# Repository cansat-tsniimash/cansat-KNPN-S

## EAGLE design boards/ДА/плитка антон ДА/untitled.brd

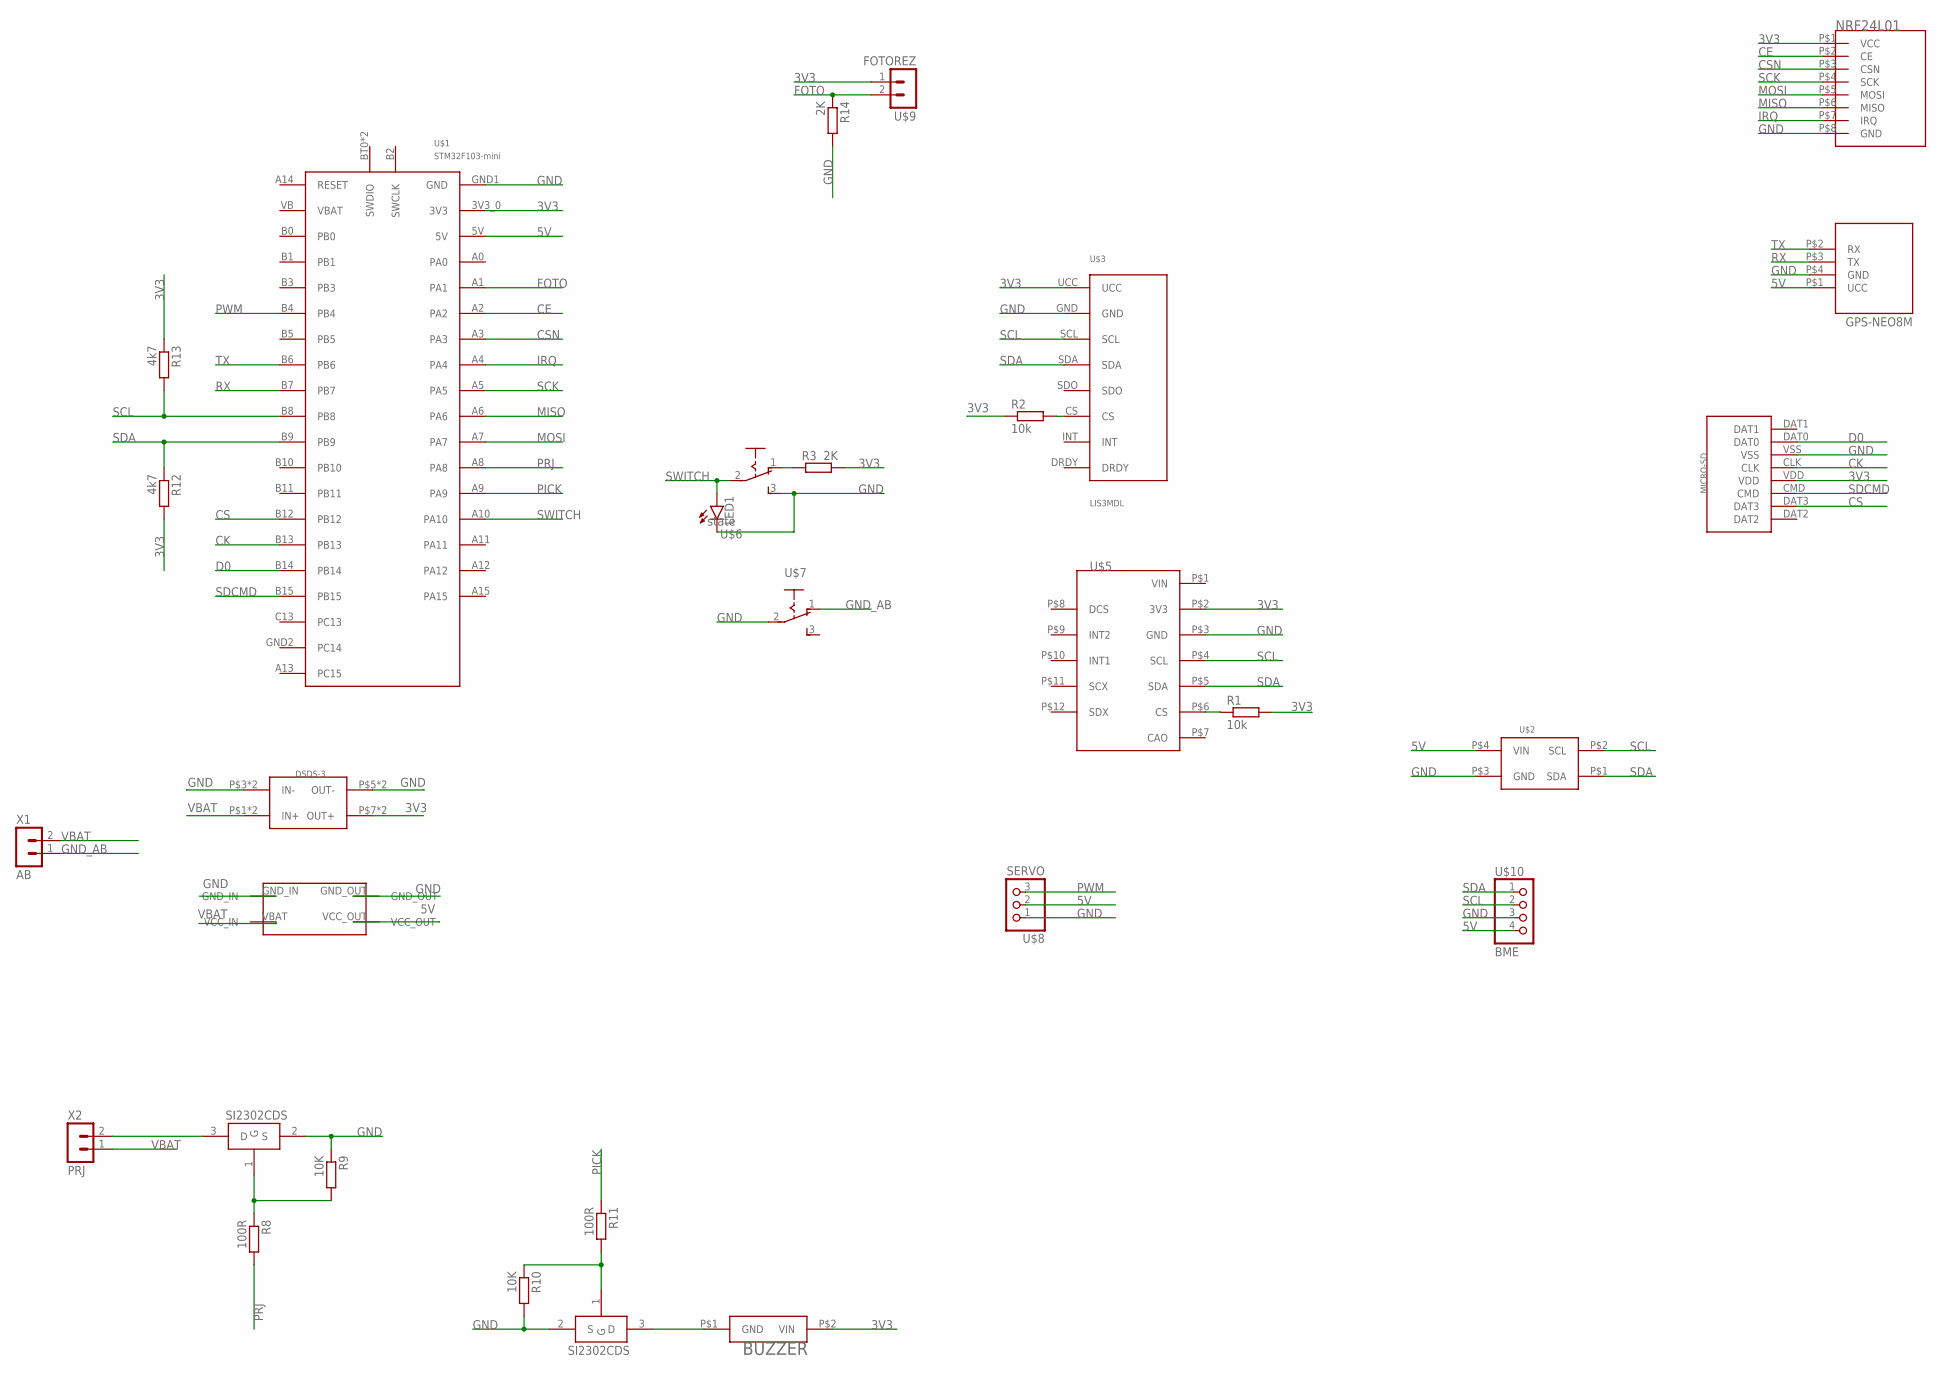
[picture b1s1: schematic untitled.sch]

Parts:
BUZZER: BUZZERS8R6; BUZZER-S8R12
DSDS-3: MP1584-B
DSDS-5: DS-DS_5V
GPS-NEO8M: GPS-NEO8M; GPS-NEO7M
LED1: LEDCHIP-LED0603; CHIP-LED0603
MICRO-SD: SD
NRF24L01: NRF24L01_ML01SP4
R1, R2: 10k; R0603
R3, R14: 2K; R0603
R8, R11: 100R; R0603
R9, R10: 10K; R0603
R12, R13: 4k7; R0603
U$1: STM32F103-mini; BLUEPILL2
U$2: BME280BME280-PINS-ONLY; BME280-PINS-ONLY
U$3: LIS3MDL
U$4, U$12: SI2302CDS; SOT23-3
U$5: LSM6DS3-GY
U$6: state; SWITCH_MSS
U$7: UNICS-SWITCHSS_12D11; SS_12D11
U$8: SERVO; 53047-03
U$9: FOTOREZ; 53047-02
U$10: BME; 53047-04
X1: AB; JST-2-2.5
X2: PRJ; JST-2-2.5

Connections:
3V3: BUZZER.P$2 (VIN), DSDS-3.P$7 (OUT+), DSDS-3.P$8 (OUT+), MICRO-SD.VDD, NRF24L01.P$1 (VCC), R1.2, R2.1, R3.1, R12.2, R13.1, U$1.3V3_0 (3V3), U$3.UCC, U$5.P$2 (3V3), U$9.1
5V: DSDS-5.VCC_OUT, GPS-NEO8M.P$1 (UCC), U$1.5V, U$2.P$4 (VIN), U$8.2, U$10.4
CE: NRF24L01.P$2 (CE), U$1.A2
CK: MICRO-SD.CLK, U$1.B13
CS: MICRO-SD.DAT3, U$1.B12
CSN: NRF24L01.P$3 (CSN), U$1.A3
D0: MICRO-SD.DAT0, U$1.B14
FOTO: R14.1, U$1.A1, U$9.2
GND: DSDS-3.P$3 (IN-), DSDS-3.P$4 (IN-), DSDS-3.P$5 (OUT-), DSDS-3.P$6 (OUT-), DSDS-5.GND_IN, DSDS-5.GND_OUT, GPS-NEO8M.P$4 (GND), LED1.C, MICRO-SD.VSS, NRF24L01.P$8 (GND), R9.1, R10.2, R14.2, U$1.GND1 (GND), U$2.P$3 (GND), U$3.GND, U$4.2 (S), U$5.P$3 (GND), U$6.3 (S), U$7.2, U$8.1, U$10.3, U$12.2 (S)
GND_AB: U$7.1 (O), X1.1
IRQ: NRF24L01.P$7 (IRQ), U$1.A4
MISO: NRF24L01.P$6 (MISO), U$1.A6
MOSI: NRF24L01.P$5 (MOSI), U$1.A7
unnamed: R3.2, U$6.1 (O)
unnamed: R1.1, U$5.P$6 (CS)
unnamed: BUZZER.P$1 (GND), U$4.3 (D)
unnamed: R8.1, R9.2, U$12.1 (G)
unnamed: U$12.3 (D), X2.2
unnamed: R10.1, R11.2, U$4.1 (G)
unnamed: R2.2, U$3.CS
PICK: R11.1, U$1.A9
PRJ: R8.2, U$1.A8
PWM: U$1.B4, U$8.3
RX: GPS-NEO8M.P$3 (TX), U$1.B7
SCK: NRF24L01.P$4 (SCK), U$1.A5
SCL: R13.2, U$1.B8, U$2.P$2 (SCL), U$3.SCL, U$5.P$4 (SCL), U$10.2
SDA: R12.1, U$1.B9, U$2.P$1 (SDA), U$3.SDA, U$5.P$5 (SDA), U$10.1
SDCMD: MICRO-SD.CMD, U$1.B15
SWITCH: LED1.A, U$1.A10, U$6.2
TX: GPS-NEO8M.P$2 (RX), U$1.B6
VBAT: DSDS-3.P$1 (IN+), DSDS-3.P$2 (IN+), DSDS-5.VBAT (VCC_IN), X1.2, X2.1

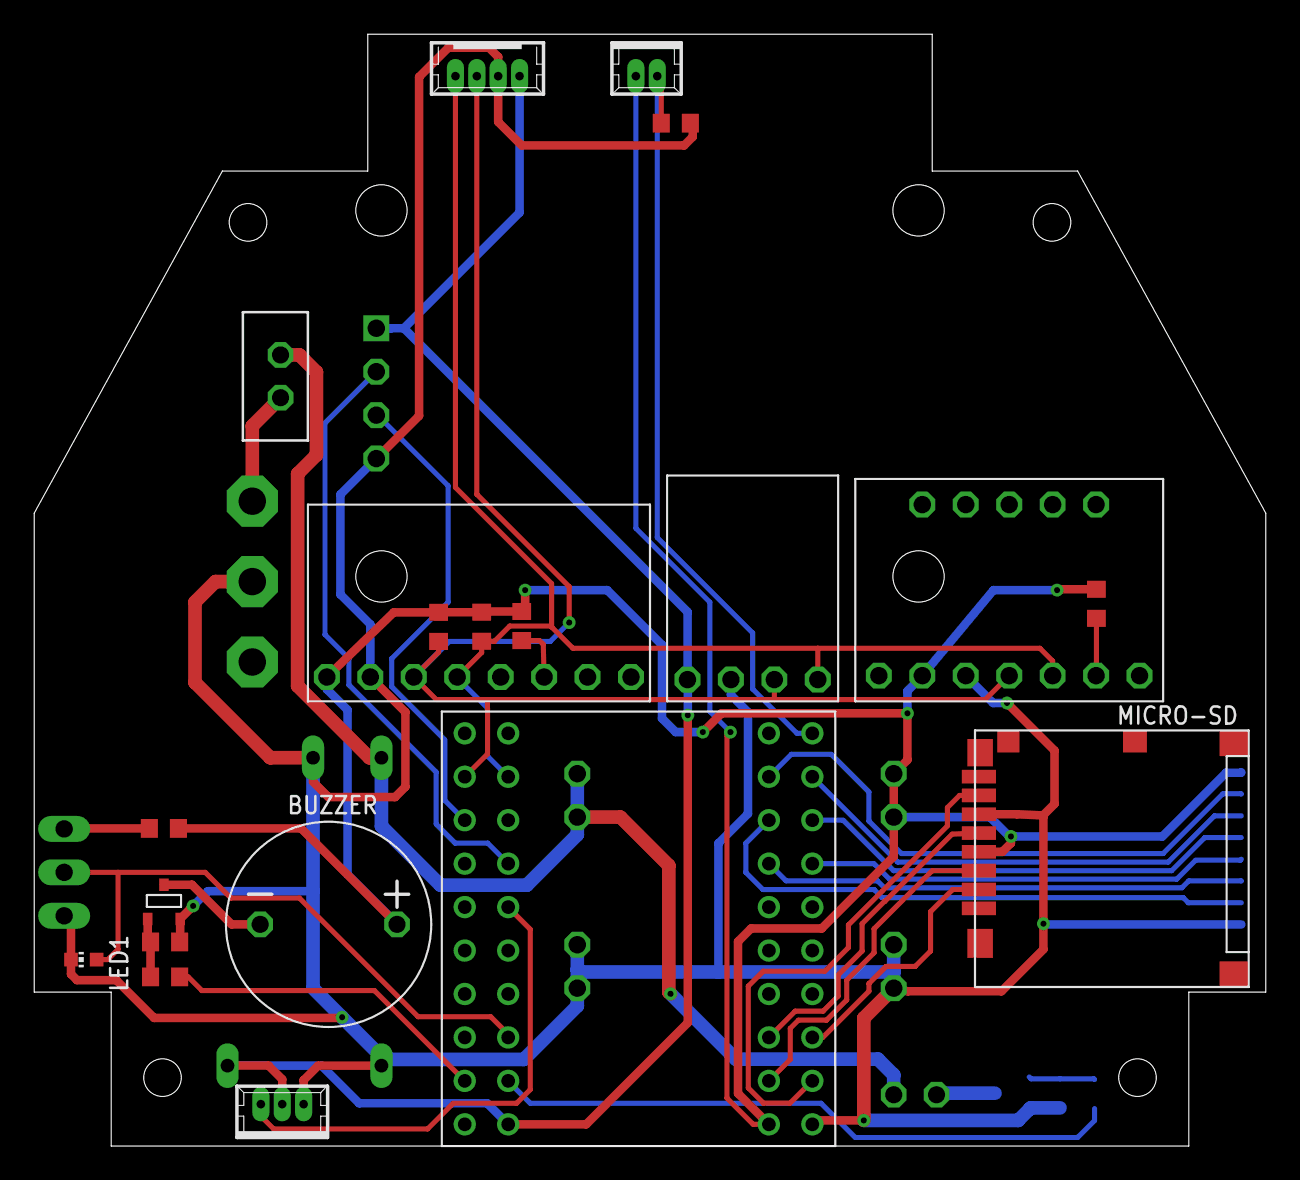
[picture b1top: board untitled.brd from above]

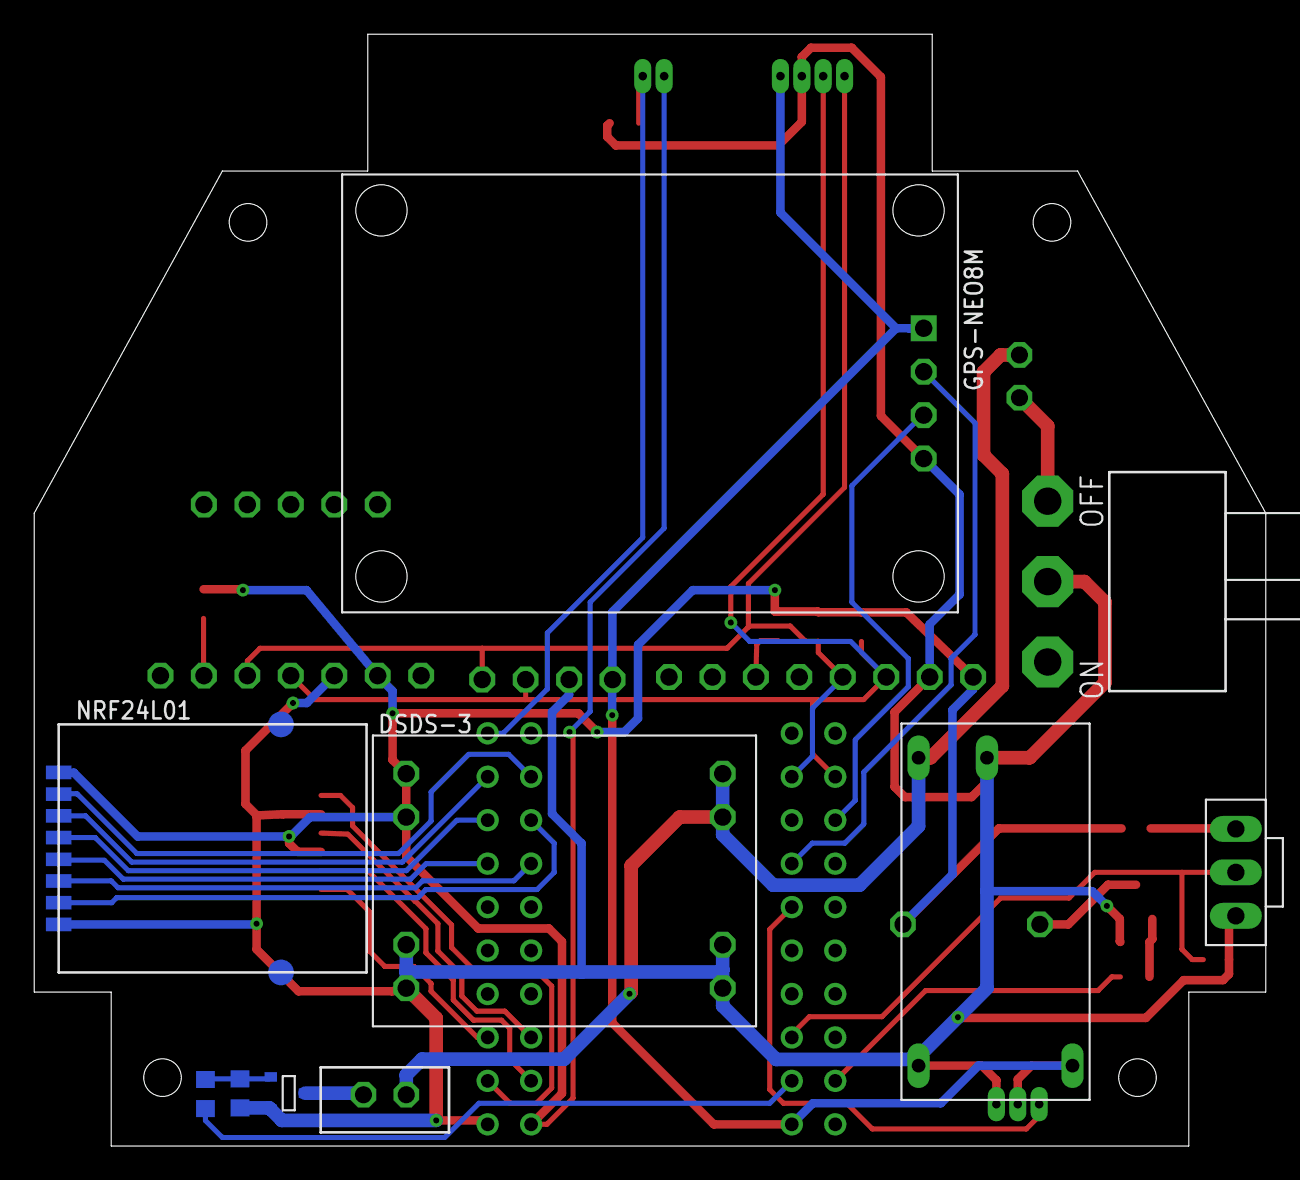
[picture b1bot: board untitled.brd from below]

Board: 2 copper layers, 72.0 x 65.0 mm, 30 parts (10 on the bottom side), 31 nets.

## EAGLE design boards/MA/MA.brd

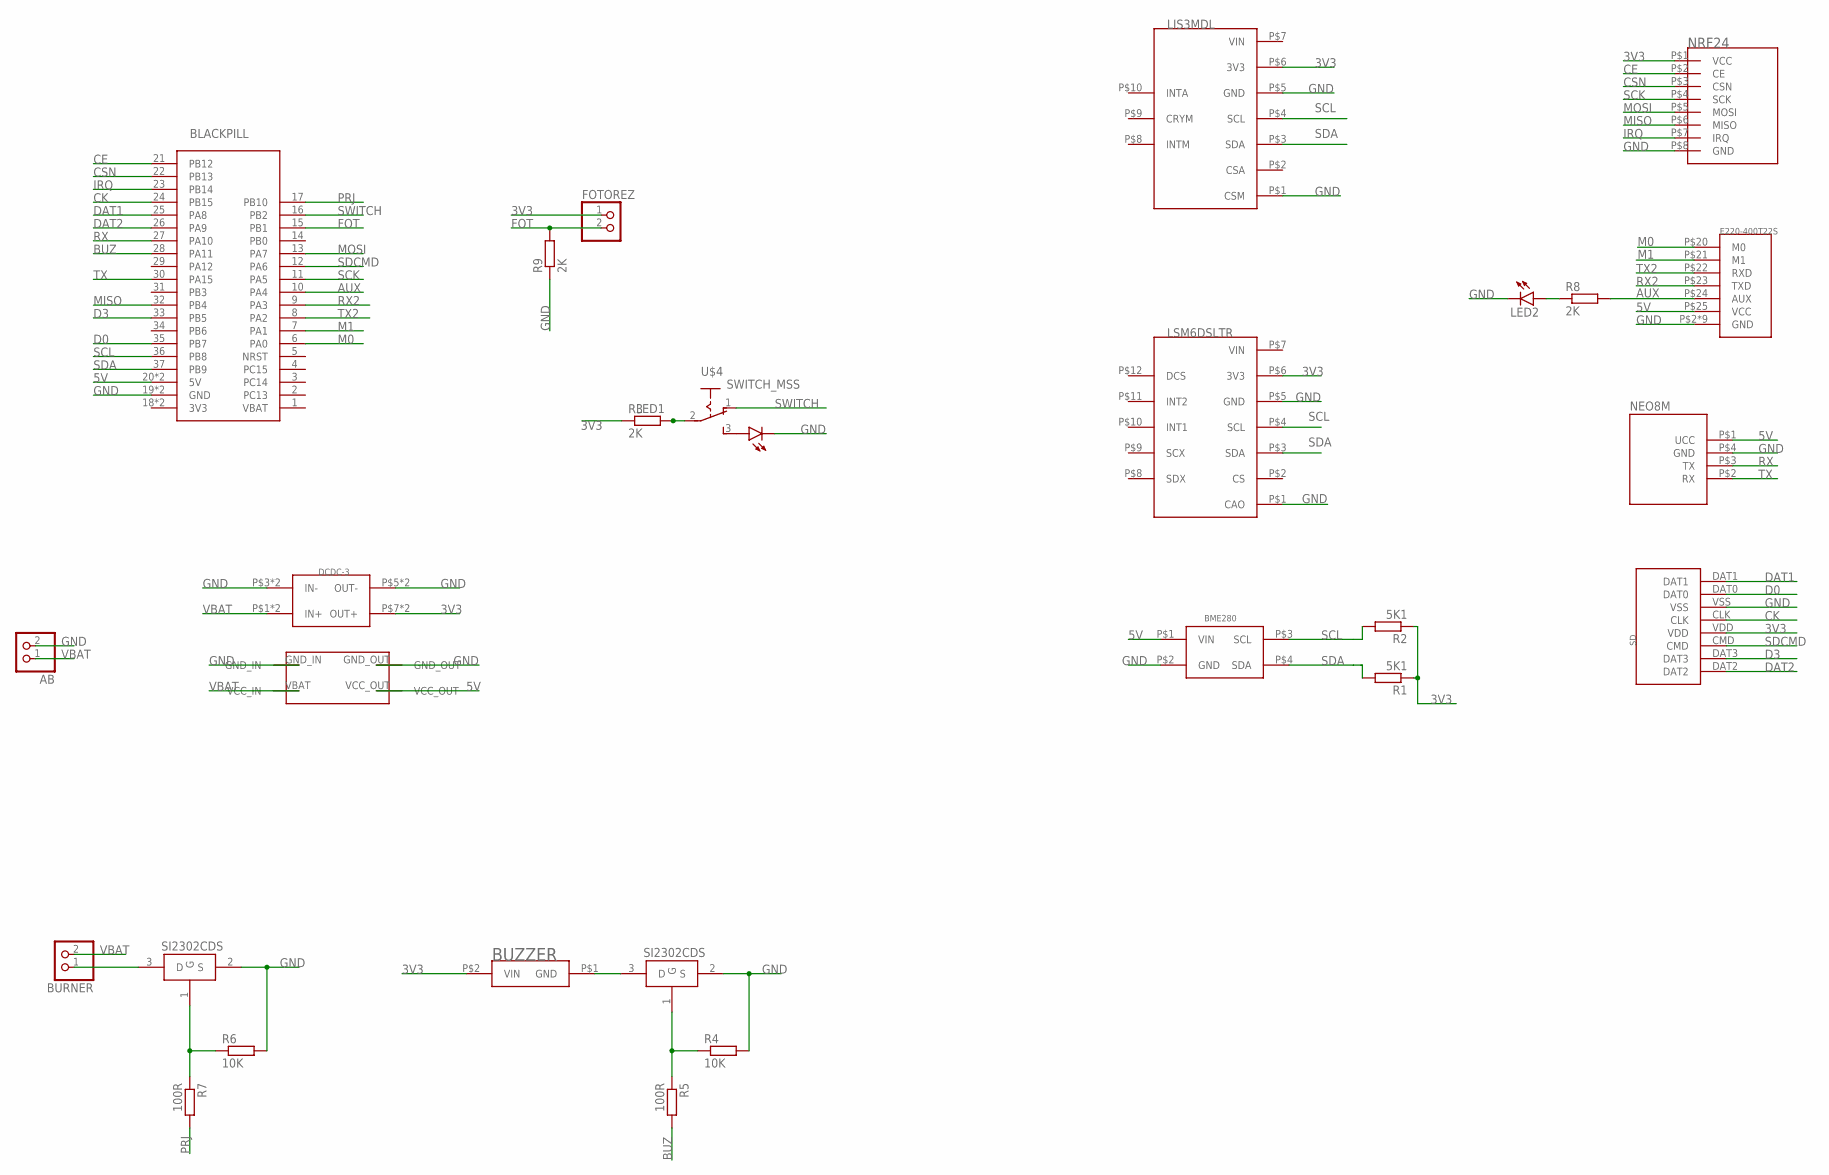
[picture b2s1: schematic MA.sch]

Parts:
AB: PINHD-1X2; 1X02
BLACKPILL: STM32F411_BOARD
BME280: BME280
BURNER: PINHD-1X2; 1X02
BUZZER: BUZZERS8R6; BUZZER-S8R12
DCDC-3: MP1584-B
E220-400T22S: E220-400T22S
FOTOREZ: PINHD-1X2; 1X02
LED1, LED2: LEDCHIP-LED0603; CHIP-LED0603
LIS3MDL: LIS3MDL-GY
LSM6DSLTR: LSM6DS3-GY
NEO8M: GPS-NEO7M
NRF24: NRF24L01_ML01SP4
R1, R2: 5K1; R0603
R3, R8, R9: 2K; R0603
R4, R6: 10K; R0603
R5, R7: 100R; R0603
SD: SD
U$1: DS-DS_5V
U$2, U$3: SI2302CDS; SOT23-3
U$4: SWITCH_MSS

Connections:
3V3: BUZZER.P$2 (VIN), DCDC-3.P$7 (OUT+), DCDC-3.P$8 (OUT+), FOTOREZ.1, LIS3MDL.P$6 (3V3), LSM6DSLTR.P$6 (3V3), NRF24.P$1 (VCC), R1.1, R2.1, R3.1, SD.VDD
5V: BLACKPILL.20 (5V), BLACKPILL.38 (5V), BME280.P$1 (VIN), E220-400T22S.P$25 (VCC), NEO8M.P$1 (UCC), U$1.VCC_OUT
AUX: BLACKPILL.10 (PA4), E220-400T22S.P$24 (AUX), R8.2
BUZ: BLACKPILL.28 (PA11), R5.2
CE: BLACKPILL.21 (PB12), NRF24.P$2 (CE)
CK: BLACKPILL.24 (PB15), SD.CLK
CSN: BLACKPILL.22 (PB13), NRF24.P$3 (CSN)
D0: BLACKPILL.35 (PB7), SD.DAT0
D3: BLACKPILL.33 (PB5), SD.DAT3
DAT1: BLACKPILL.25 (PA8), SD.DAT1
DAT2: BLACKPILL.26 (PA9), SD.DAT2
FOT: BLACKPILL.15 (PB1), FOTOREZ.2, R9.2
GND: AB.2, BLACKPILL.19 (GND), BLACKPILL.39 (GND), BME280.P$2 (GND), DCDC-3.P$3 (IN-), DCDC-3.P$4 (IN-), DCDC-3.P$5 (OUT-), DCDC-3.P$6 (OUT-), E220-400T22S.P$2 (GND), E220-400T22S.P$8 (GND), E220-400T22S.P$11 (GND), E220-400T22S.P$13 (GND), E220-400T22S.P$14 (GND), E220-400T22S.P$15 (GND), E220-400T22S.P$16 (GND), E220-400T22S.P$19 (GND), E220-400T22S.P$26 (GND), LED1.C, LED2.C, LIS3MDL.P$1 (CSM), LIS3MDL.P$5 (GND), LSM6DSLTR.P$1 (CAO), LSM6DSLTR.P$5 (GND), NEO8M.P$4 (GND), NRF24.P$8 (GND), R4.2, R6.2, R9.1, SD.VSS, U$1.GND_IN, U$1.GND_OUT, U$2.2 (S), U$3.2 (S)
IRQ: BLACKPILL.23 (PB14), NRF24.P$7 (IRQ)
M0: BLACKPILL.6 (PA0), E220-400T22S.P$20 (M0)
M1: BLACKPILL.7 (PA1), E220-400T22S.P$21 (M1)
MISO: BLACKPILL.32 (PB4), NRF24.P$6 (MISO)
MOSI: BLACKPILL.13 (PA7), NRF24.P$5 (MOSI)
unnamed: BUZZER.P$1 (GND), U$2.3 (D)
unnamed: BURNER.1, U$3.3 (D)
unnamed: R6.1, R7.1, U$3.1 (G)
unnamed: R4.1, R5.1, U$2.1 (G)
unnamed: LED1.A, U$4.3 (S)
unnamed: R3.2, U$4.2
unnamed: LED2.A, R8.1
PRJ: BLACKPILL.17 (PB10), R7.2
RX: BLACKPILL.27 (PA10), NEO8M.P$3 (TX)
RX2: BLACKPILL.9 (PA3), E220-400T22S.P$23 (TXD)
SCK: BLACKPILL.11 (PA5), NRF24.P$4 (SCK)
SCL: BLACKPILL.36 (PB8), BME280.P$3 (SCL), LIS3MDL.P$4 (SCL), LSM6DSLTR.P$4 (SCL), R2.2
SDA: BLACKPILL.37 (PB9), BME280.P$4 (SDA), LIS3MDL.P$3 (SDA), LSM6DSLTR.P$3 (SDA), R1.2
SDCMD: BLACKPILL.12 (PA6), SD.CMD
SWITCH: BLACKPILL.16 (PB2), U$4.1 (O)
TX: BLACKPILL.30 (PA15), NEO8M.P$2 (RX)
TX2: BLACKPILL.8 (PA2), E220-400T22S.P$22 (RXD)
VBAT: AB.1, BURNER.2, DCDC-3.P$1 (IN+), DCDC-3.P$2 (IN+), U$1.VBAT (VCC_IN)

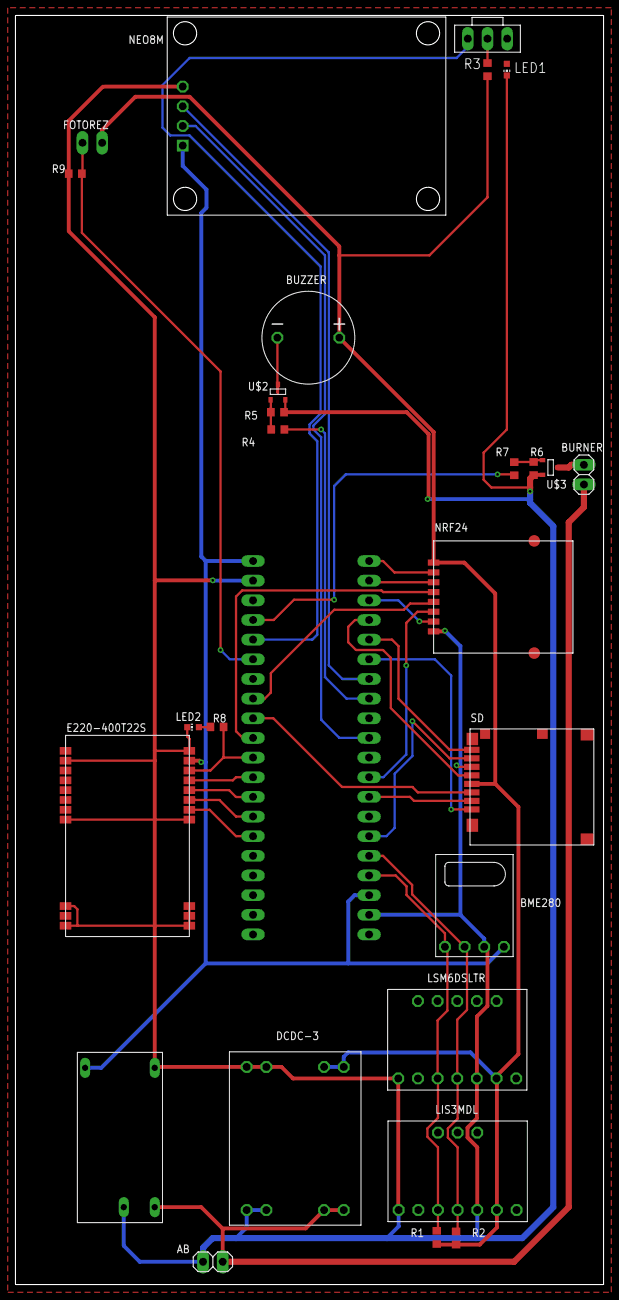
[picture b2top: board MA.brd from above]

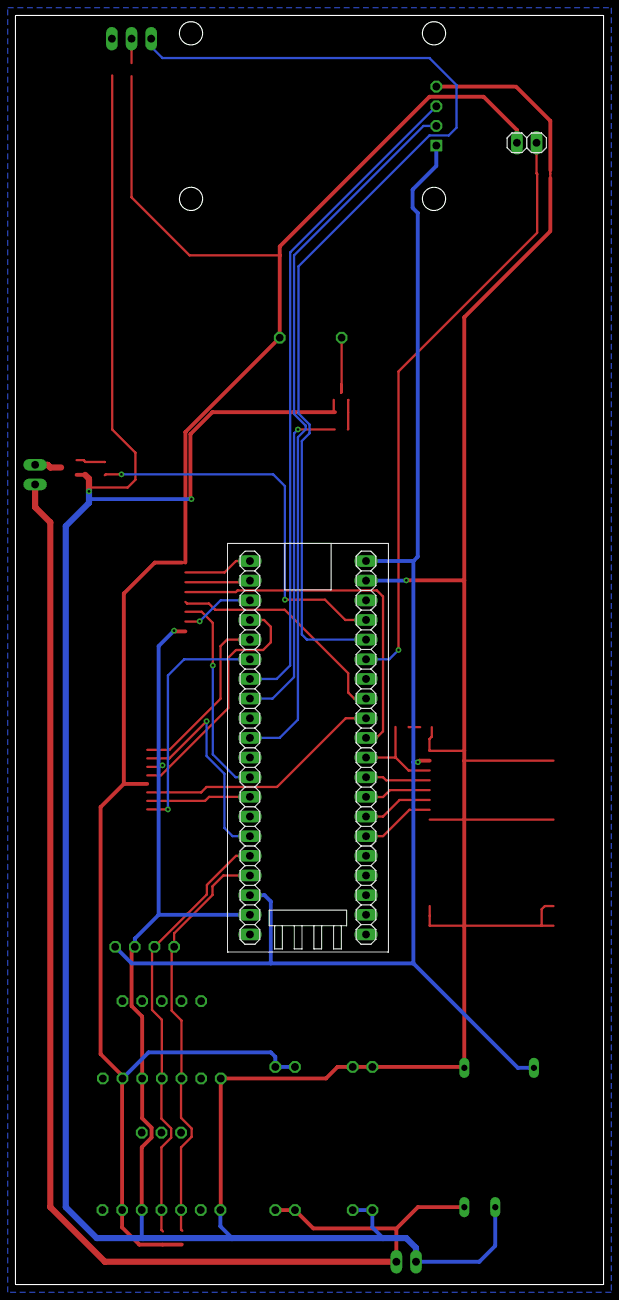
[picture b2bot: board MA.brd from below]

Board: 2 copper layers, 76.0 x 164.0 mm, 28 parts (2 on the bottom side), 36 nets.

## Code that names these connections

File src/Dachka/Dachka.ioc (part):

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Mcu.Name=STM32F103C(8-B)Tx
Mcu.Package=LQFP48
Mcu.UserName=STM32F103C8Tx
PA1.Signal=ADCx_IN1
PA10.Signal=GPIO_Input
PA13.Mode=Serial_Wire
PA13.Signal=SYS_JTMS-SWDIO
PA14.Mode=Serial_Wire
PA14.Signal=SYS_JTCK-SWCLK
PA15.Signal=GPIO_Output
PA2.GPIOParameters=GPIO_Label
PA2.GPIO_Label=CE
PA2.Signal=GPIO_Output
PA3.GPIOParameters=GPIO_Label
PA3.GPIO_Label=CSN
PA3.Signal=GPIO_Output
PA4.GPIOParameters=GPIO_Label
PA4.GPIO_Label=IRQ
PA4.Signal=GPIO_Input
PA5.Mode=Full_Duplex_Master
PA5.Signal=SPI1_SCK
PA6.Mode=Full_Duplex_Master
PA6.Signal=SPI1_MISO
PA7.Mode=Full_Duplex_Master
PA7.Signal=SPI1_MOSI
PA8.GPIOParameters=GPIO_Label
PA8.GPIO_Label=PRJ
PA8.Signal=GPIO_Output
PA9.GPIOParameters=GPIO_Label
PA9.GPIO_Label=PICK
PA9.Signal=GPIO_Output
PB12.GPIOParameters=GPIO_Label
PB12.GPIO_Label=CS
PB12.Signal=GPIO_Output
PB13.Mode=Full_Duplex_Master
PB13.Signal=SPI2_SCK
PB14.Mode=Full_Duplex_Master
PB14.Signal=SPI2_MISO
PB15.Mode=Full_Duplex_Master
PB15.Signal=SPI2_MOSI
PB4.Signal=S_TIM3_CH1
PB6.Mode=Asynchronous
PB6.Signal=USART1_TX
PB7.Mode=Asynchronous
PB7.Signal=USART1_RX
PB8.Mode=I2C
PB8.Signal=I2C1_SCL
PB9.Mode=I2C
PB9.Signal=I2C1_SDA
PC13-TAMPER-RTC.Signal=GPIO_Output
RCC.SYSCLKFreq_VALUE=64000000
RCC.SYSCLKSource=RCC_SYSCLKSOURCE_PLLCLK
board=custom

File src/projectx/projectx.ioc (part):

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Mcu.Name=STM32F411C(C-E)Ux
Mcu.Package=UFQFPN48
Mcu.UserName=STM32F411CEUx
PA0-WKUP.Signal=GPIO_Output
PA1.Signal=GPIO_Output
PA10.Mode=Asynchronous
PA10.Signal=USART1_RX
PA11.GPIOParameters=GPIO_Label
PA11.GPIO_Label=pick
PA11.Signal=GPIO_Output
PA13.Mode=Serial_Wire
PA13.Signal=SYS_JTMS-SWDIO
PA14.Mode=Serial_Wire
PA14.Signal=SYS_JTCK-SWCLK
PA15.Mode=Asynchronous
PA15.Signal=USART1_TX
PA2.Mode=Asynchronous
PA2.Signal=USART2_TX
PA3.Mode=Asynchronous
PA3.Signal=USART2_RX
PA4.Signal=GPIO_Input
PA5.Mode=Full_Duplex_Master
PA5.Signal=SPI1_SCK
PA6.Mode=SD_1_bit
PA6.Signal=SDIO_CMD
PA7.Mode=Full_Duplex_Master
PA7.Signal=SPI1_MOSI
PB1.Signal=ADCx_IN9
PB10.Signal=GPIO_Output
PB12.GPIOParameters=GPIO_Label
PB12.GPIO_Label=CE
PB12.Signal=GPIO_Output
PB13.GPIOParameters=GPIO_Label
PB13.GPIO_Label=CSN
PB13.Signal=GPIO_Output
PB15.Mode=SD_1_bit
PB15.Signal=SDIO_CK
PB2.GPIOParameters=GPIO_Label
PB2.GPIO_Label=switck
PB2.Signal=GPIO_Input
PB4.Mode=Full_Duplex_Master
PB4.Signal=SPI1_MISO
PB7.Mode=SD_1_bit
PB7.Signal=SDIO_D0
PB8.Mode=I2C
PB8.Signal=I2C1_SCL
PB9.Mode=I2C
PB9.Signal=I2C1_SDA
PC13-ANTI_TAMP.Signal=GPIO_Output
RCC.HSE_VALUE=25000000
RCC.SYSCLKFreq_VALUE=100000000
RCC.SYSCLKSource=RCC_SYSCLKSOURCE_PLLCLK
board=custom

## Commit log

2025-10-11 проба пера
2025-10-11 проба модели
2025-10-11 добавил отсек электроники и обозначил отсек под камеру . Саня тайлер дёрден
2025-10-31 жудалил нахуй уже 4 раз старую версию и вот мой больничный набросок .
2025-11-04 Planer part
2025-11-05 добавил код на гит(ура)
2025-11-05 Был убран лишний код, сделали инициализацию bme отдельно, bme работает штатно :)
2025-11-05 Добавлен .gitignore, проект переехал в отдельную папку :)
2025-11-05 пиво
2025-11-07 мой первый камит
2025-11-12 более детальная проработка конструкции .
2025-11-12 прибрал за собой . клин работает проработал новы конст элементы пиво
2025-11-12 удалил фойл ошибки . пиво
2025-11-12 всё что есть по планеру
2025-11-14 Настроил ioc clock на 100 мгц + lsm6ds3 работает + фоторезистор работает
2025-11-14 Выполнил расчет радиолинии МА И ДА(текстовый формат и две картинки под МА и ДА)
2025-11-14 планер в крео ЕСТЬ
2025-11-14 рассчитал состав пакетов МА и ДА (1 пакет МА и 3 пакета ДА)
2025-11-14 добавлены:прижимная пластина гпс , квадрат радиомаяка , креплдение радиомаяка + улучшения в общей конструкции. пиво
2025-11-15 Исправил расчёт радиолинии ДА
2025-11-15 Добавил код для NEO8m + сделал схему подключения ма (Антон сделал схему подключения ДА)
2025-11-15 поправил пакеты, поправил схему подключения да, поправил схему подключения ма, сделал алгоритм работы аппарата
2025-11-19 добавил дырки под парашют после печати первого прототипа исправил тонкие места и изменил крепление акума на горизонтальное ( было вертикальное ) пиво .
2025-11-21 добавил алгорит работы аппарата да
2025-11-22 внутренности планера
2025-11-22 и ещё чуть-чуть
2025-11-26 глидер, хз на всякий слючай
2025-11-28 разобрались с глидерами
2025-11-28 куча моделек для плат
2025-11-29 сделал плату . всё
2025-11-29 поправил алгорит работы да, ма. поправил схему подключения да, ма. внес изменения в ioc файл. сделал программу палета. сделал схему обмена данными ма да
2025-12-03 сделаль разрезики подо всякое в планере
2025-12-05 сделал расчеты ма-земля(ма-да) + исправил схему подключения ма + (в пакеты.xlsx сделал там таблицы для слайдов расчета радиолинии мада маземля)
2025-12-05 поправил gps
2025-12-06 gleder level up
2025-12-06 glider max level up
2025-12-12 glider max 8
2025-12-12 update 2
2025-12-12 разукрасил все элементы красиво добавил акумы и напонение элементной бызы на сборке .
2025-12-12 сделал вырез под вал и другие изменения но не помню какие.
2025-12-12 update 3
2025-12-12 update 4
2025-12-17 сделал дирочку под вальчик .
2025-12-17 удалил старые версии деталей
2025-12-17 подправил размерчики в планере
2025-12-19 Я СДЕЛАЛ ПЛАТЫ С ВРОДЕ НОРМ РАСПИНОВКОЙ И ПОДКЛЮЧЕНИЯМИ . ЕСТЬ ВСЁ КРОМЕ ФОТОРЕЗИСТОРА И ДС-ДС НА 5 ВОЛЬТ
2025-12-19 радио работает
2025-12-19 косметические процедуры
2025-12-23 доделал платы до приемлемого уровня.
2025-12-24 тех нужды
2025-12-24 e yfc yfrjytw nj dktpftn gkfyth? hfleqntcm
2025-12-24 Нос планера
2025-12-24 Рабочее состояние!
2025-12-24 Вот теперь точно рабочее состояние
2025-12-24 Очищены бекапы крео
2025-12-24 сииильно всё работает
2025-12-24 схемка
2025-12-24 nos планера
2025-12-24 new nosi
2025-12-26 new Нос
2026-01-06 no problems
2026-01-06 поменял наконец длину
2026-01-06 возможны проблемы
2026-01-10 схемочки (Здесь были видосики Андрея, но гитхаб не захотел кушать гиги свежей информации)
2026-01-10 Сделала алгоритмы читаемыми
2026-01-16 незначительные изменения по конструкции . Ошибка слишком большая длинна ДА в следующем кимите исправлена .
2026-01-16 так ну расказ будет наверное долгим. сделал отверстие под переключатель состояний . переделал отверстие под фоторезистор и переставил его на правильную сторону . сделал бортики для да для того ччтобы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
2026-01-31 Сделано система САС ДА . всё .
2026-02-14 добавил серву и пару схемочек
2026-02-14 покромсал фюзеляж, изменил крепление платы
2026-02-14 Хватит коммитить гигобайты свежего мусора
2026-02-14 New vision - New possibilities - New glider
2026-02-18 GPS работает, Мария удалила лишнее
2026-02-18 код на ДА радио начало
2026-02-18 Выгрузил модель пусковой установки
2026-02-18 Изменения в глидере
2026-02-21 Рабочая ГПС
2026-02-21 новый ioc матки
2026-02-21 ещё изменений в глидере
2026-02-23 Произведена перекомпоновка планера
2026-02-25 Компоновка платы, серва в говне
2026-02-27 Осталось вырезать дырку под пережигатель и конструкция будет готова
2026-02-28 Наисвежайшая бомбордировка строчками новейшего кода для дочки
2026-02-28 Изменил одну строчку
2026-02-28 Потерял файлы по дороге
2026-02-28 ФИНАЛЬНАЯ КОНСТРУКЦИЯ ДОЧКИИИИИИ
2026-03-01 Не совсем финальная конструкция ДА
2026-03-04 Привел модель платы ДА в соответствии с разводкой в Eagle. И шкив поправил
2026-03-04 расставили компоненты на плате МА и ещё по мелочи
2026-03-06 поменял массу и ещё по мелочи
2026-03-07 lsm6ds3
2026-03-07 пару размерчиков подправил
2026-03-13 Начало флешки, дописан датчик lis3mdl
2026-03-13 У ДА надо поменять профиль хвоста, правильно разместить компоненты на плате, сделать вырезы под них в корпусе
2026-03-14 SD работает
2026-03-20 матка на проверку .
2026-03-20 test
2026-03-20 РАбочее бортовое радио. Мега рассылка на частоте 453 Ггц
2026-03-20 наземка
2026-03-20 чуть-чуть для пусковой
2026-03-21 Модели крыльев адаптированы для печати
2026-03-21 может пичинится комит, хз
2026-03-21 крылья починены
2026-03-25 надеюсь вячеслав увидит новый камит .
2026-03-26 Комит для Кирилла
2026-03-26 чутка размерчиков
2026-04-08 Телеметрия и немного стлек
2026-04-08 Поправил табы
2026-04-08 3 файла не помещаются, переписываем на 2 + исправлены пакеты и запись времени
2026-04-08 Фоторезистор рабтает
2026-04-08 Тест сервопривода - работает
2026-04-10 НАчало пересчёта, рабочая трубка пито
2026-04-10 Cделал пережигатель чуть более энергозатратным на 170 мс
2026-04-10 Ну пережигатель теперь работает 2секунды
2026-04-11 переписал фоторезистор чтоб давал мегалюксы
2026-04-11 Начал писать нормальный сервопривод, но тот не работает. Возможно не работает потому что что-то неправильно написано
2026-04-11 Я забыл вставить иницилизацию сервы, теперь код работает
2026-04-11 НУжно кстати подумать как нормально считать угол хвоста. При значении b = -153 он не крутится. а так ок
2026-04-11 НУ ещё вроде дописал состоянья
2026-04-11 Улучшение сервы
2026-04-11 Добавил check сумму, мой пересчёт фоторезистора в мегаlux не работает. Я stop на сырых datas
2026-04-24 радио дочки даёт газ в эфир
2026-04-25 добавил канавку под пережигатель и какие то рёбра жёскости . P.s совершенно беполезные
2026-04-26 Новый хвост планера
2026-04-26 Глупый саблайм. Ему говорят взять мою модель (ours), а не серверную (theirs), а он всё равно серверную берет и удаляет всё, что я сдела
2026-04-30 Сделал правильные вырезы в корпусе планера, добавил местоа позиционирования на стыке деталей, добавил гравировку, скрыл линии
2026-04-30 На 1 мм подвинул гайку. Это очень важно
2026-05-07 КИРИЛЛ! Я поменял крышку. Обрати внимание
2026-05-11 массу подправил на матери чутка
2026-05-11 Наисвежайшая бомбордировка отборным кодом
2026-05-11 Состояния вроде ок, пережигатель код (возможно не робит,а может робит)
2026-05-12 Исправил ошибки с размерами гаек
2026-05-13 Оказывается пережигатель работает очень даже хорошо, поправил код для дочки с сервой. Занулил его после включения
2026-05-14 Дочка батрачит нормально
2026-05-22 Допиливаем, чтобы ДА собирался, а МА мог стоять в ракете вверх ногами
2026-05-22 изменения в телеметрии, стлки
2026-05-22 самая наипоследняйшая версия кодов
2026-05-23 мелкие изменения в крыльях, крышка для пережигателя
2026-05-31 В отдельной папке добавлен вариант V-планера
2026-06-05 +графики на наземку и модель планера которая крутится. Запись на сд карту пакетов ДА на МА
2026-06-06 новая наземка
2026-06-12 СЕрва работает, + код для наземки
2026-06-12 ЕЩё порция кода для наземки
2026-06-12 новый угол планера
2026-06-12 стлки и неактуальные изменения в крыльях
2026-06-12 телеметрия вторых пусков планера
2026-06-16 Переделал крышку МА под V-планер с углом 7 градусов
2026-06-20 новая земля
2026-06-20 землю красивая
2026-06-26 Всё работает
2026-06-26 крутая скорость радио
